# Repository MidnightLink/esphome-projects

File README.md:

This repo is for changes done to the Velux controller. USB-C has been added in place of the barrel plug

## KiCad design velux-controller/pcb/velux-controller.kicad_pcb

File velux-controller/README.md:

# ESPHome Velux Controller

This project has been edited to include USB C for power. Note that you must either use your own custom power supply, or use a USB A to C cable to get the 5V as it's just a connector and doesn't include any PD system

This project modifies a Velux KLI 310 or similar remote control to integrate with home assistant.
It replaces the back panel of the original remote, powers it from the wall, and can report state back to home assistant even if you press the physical buttons.

Installing it on the remote only requires removing the back and batteries, soldering 5 wires and plugging it into the control board. This process is nondestructive and reversible.

It runs on anywhere between 5V and 12V, though 5V is preferred.

**Photos not of new USB C Version**

## Bill of Materials

- 1x ESP-12F module
	([Mouser](https://eu.mouser.com/ProductDetail/Adafruit/2491?qs=N%2F3wi2MvZWDVFv7HwruvGQ%3D%3D),
	[AliExpress](https://www.aliexpress.com/item/1005004495916418.html))
- 1x SOT223 AMS1117-3.3 linear voltage regulator
	([DigiKey](https://www.digikey.com/en/products/detail/texas-instruments/TLV1117LV33DCYR/2666508),
	[AliExpress](https://www.aliexpress.com/item/1005004529378722.html))
- 3x SOT23 MMBT3904 transistor
	([DigiKey](https://www.digikey.com/en/products/detail/diotec-semiconductor/MMBT3904/20391048),
	[AliExpress](https://www.aliexpress.com/item/1005002334131697.html))
- 8x 0603 10kΩ resistor
	([DigiKey](https://www.digikey.com/en/products/detail/stackpole-electronics-inc/RMCF0603FT10K0/1761235),
	[AliExpress](https://www.aliexpress.com/item/32867298442.html))
- 6x 0603 1kΩ resistor
	([DigiKey](https://www.digikey.com/en/products/detail/stackpole-electronics-inc/RMCF0603FT1K00/1761077),
	[AliExpress](https://www.aliexpress.com/item/32867298442.html))
- 2x 0805 100nF ceramic capacitor
	([DigiKey](https://www.digikey.com/en/products/detail/samsung-electro-mechanics/CL21B104KACNNNC/3886757),
	[AliExpress](https://www.aliexpress.com/item/32964553793.html))
- 1x SMA 22μF tantalum capacitor
	([DigiKey](https://www.digikey.com/en/products/detail/kemet/T491A226M010AT/818553),
	[AliExpress](https://www.aliexpress.com/item/1005006136419609.html))
- 2x PTS820 tactile switch
	([DigiKey](https://www.digikey.com/en/products/detail/cit-relay-and-switch/CS1213AGF160/16607723),
	[AliExpress](https://www.aliexpress.com/item/1005004307665595.html))
- 1x USB4125 - USB Charging Connector Type C Horizontal 
	([DigiKey](https://www.digikey.com/en/products/detail/gct/USB4125-GF-A/13547388),
	[AliExpress](https://www.aliexpress.us/item/3256808142228900.html?gatewayAdapt=glo2usa4itemAdapt))
- 1x male pin header 1x4 2.54mm pitch
	([AliExpress](https://www.aliexpress.com/item/4000857385112.html))
- 1x 2Pin JST-XH connector pair, right angle
	([DigiKey](https://www.digikey.com/en/products/detail/jst-sales-america-inc/S2B-XH-A-1/9961922),
	AliExpress [assortment](https://www.aliexpress.com/item/1005006498660940.html) + [right angle](https://www.aliexpress.com/item/1005004067623293.html))
- 1x 3Pin JST-XH connector pair, right angle
	([DigiKey](https://www.digikey.com/en/products/detail/jst-sales-america-inc/S3B-XH-A-1/1556255),
	AliExpress [assortment](https://www.aliexpress.com/item/1005006498660940.html) + [right angle](https://www.aliexpress.com/item/1005004067623293.html))
- spare wire + JST-XH crimps
	([AliExpress assortment](https://www.aliexpress.com/item/1005006498660940.html))
- 4x M2x6mm coarse thread screws, pan head
	([AliExpress](https://www.aliexpress.com/item/33043885403.html))
- 4x M2 paper washers
	([AliExpress](https://www.aliexpress.com/item/1005003052657995.html))

I didn't need these, but you can add them if your ESP is unhappy with the supply voltage:

> Note: It isn't super obvious from the footprints, but these additional capacitors are supposed to mount horizontally against the board facing toward the bottom. If mounted vertically they may prevent the case from being closed.

- 1x 470μF >=5V electrolytic capacitor, 2mm pitch
	([DigiKey](https://www.digikey.com/en/products/detail/wurth-elektronik/860010273011/5726952),
	[AliExpress assortment](https://www.aliexpress.com/item/1940215752.html))
- 1x 10μF >=16V electrolytic capacitor, 1.5mm pitch
	([DigiKey](https://www.digikey.com/en/products/detail/nichicon/UVR1C100MDD6TP/4328964),
	[AliExpress assortment](https://www.aliexpress.com/item/1940215752.html))

## Attribution
Thanks to these fine people for their research on how to interface with the remote control:
- https://ottelo.jimdofree.com/velux-integra-esp8266/
- https://www.reddit.com/r/homeassistant/comments/pzhkia/hack_velux_kli3xx_to_use_blinds_without_gateway/

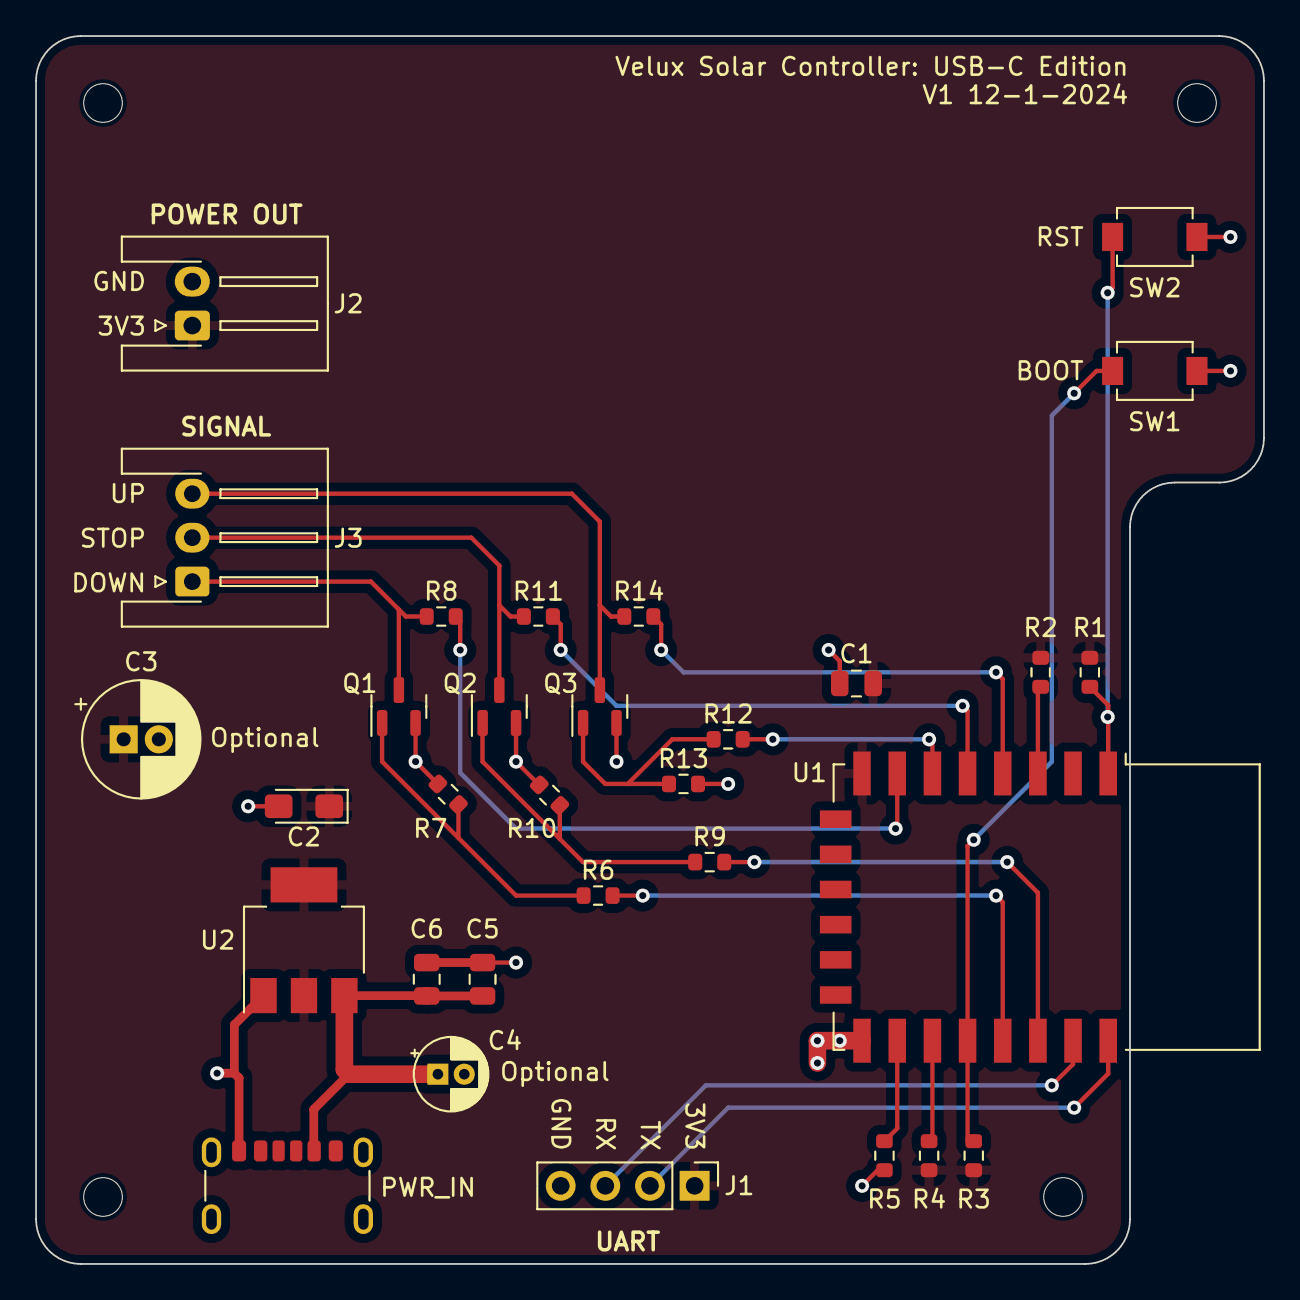
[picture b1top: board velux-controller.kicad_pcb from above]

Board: 2 copper layers, 69.9 x 69.8 mm, 35 parts (0 on the bottom side), 22 nets.

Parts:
C1, C6: 0.1μF; C_0805_2012Metric
C2: 22μF; CP_EIA-3216-10_Kemet-I_Pad1.58x1.35mm_HandSolder
C3: 470μF; CP_Radial_D6.5mm_P2.00mm
C4: 10μF; CP_Radial_D4.0mm_P1.50mm
C5: 10μF; C_0805_2012Metric
H1, H2, H3, H4: MountingHole; MountingHole_2.2mm_M2
J1: UART; PinHeader_1x04_P2.54mm_Vertical
J2: POWER OUT; JST_XH_S2B-XH-A-1_1x02_P2.50mm_Horizontal
J3: SIGNAL; JST_XH_S3B-XH-A-1_1x03_P2.50mm_Horizontal
PWR_IN: USB_C_Receptacle_GCT_USB4125-xx-x_6P_TopMnt_Horiz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; USB_C_Receptacle_GCT_USB4125-xx-x_6P_TopMnt_Horizontal
Q1, Q2, Q3: MMBT3904; SOT-23
R1, R2, R3, R4, R5, R7, R10, R13: 10K; R_0603_1608Metric
R6, R8, R9, R11, R12, R14: 1K; R_0603_1608Metric
SW1: BOOT; SW_PTS820
SW2: RST; SW_PTS820
U1: ESP-12F; ESP-12E
U2: AMS1117-3.3; SOT-223-3_TabPin2

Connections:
+3.3V: C1.2, C2.1, C3.1, J1.1, J2.1, R1.2, R2.2, R3.2, R4.2, U1.8 (VCC), U2.2 (VO)
/EN: R2.1, U1.3 (EN)
/GPIO0: R3.1, SW1.2, U1.18 (GPIO0)
/GPIO2: R4.1, U1.17 (GPIO2)
/GPIO4: R6.2, U1.19 (GPIO4)
/GPIO5: R9.2, U1.20 (GPIO5)
/GPIO12: R12.2, U1.6 (GPIO12)
/GPIO13: R8.2, U1.7 (GPIO13)
/GPIO14: R11.2, U1.5 (GPIO14)
/GPIO15: R5.2, U1.16 (GPIO15)
/GPIO16: R14.2, U1.4 (GPIO16)
/LINE_DOWN: J3.1, Q1.3 (C), R8.1
/LINE_STOP: J3.2, Q2.3 (C), R11.1
/LINE_UP: J3.3, Q3.3 (C), R14.1
/RST: R1.1, SW2.2, U1.1 (~RST)
/RXD: J1.3, U1.21 (GPIO3/RXD)
/TXD: J1.2, U1.22 (GPIO1/TXD)
GND: C1.1, C2.2, C3.2, C4.2, C5.1, C6.1, J1.4, J2.2, PWR_IN.B12, Q1.2 (E), Q2.2 (E), Q3.2 (E), R5.1, R7.2, R10.2, R13.2, SW1.1, SW2.1, U1.15 (GND), U2.1 (GND)
unnamed: Q1.1 (B), R6.1, R7.1
unnamed: Q2.1 (B), R9.1, R10.1
unnamed: Q3.1 (B), R12.1, R13.1
VCC: C4.1, C5.2, C6.2, U2.3 (VI)

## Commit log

2025-07-20 Removing other files that aren't changed. Updated Velux
